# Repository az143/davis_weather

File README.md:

this repository contains all tools necessary for building remote AND online
weather stations using davis vantage vue (or vantage pro) kit.

to be precise, this includes:

* an implementation of the workaround for the infamous "green dot" vendor
lock-in, written in C for a Microchip pic16f88 (without any external
components),

* a data gatherer program (in perl) that fetches the weather readings from a
davis console at configurable intervals, then condenses and uploads the
data to a server on the net,

* a data collector program (in perl) that listens for such uploads and saves the
data in an sqlite database, and optionally uploads it to weather underground
and/or the bom/uk-metoffice weather observations website,

* and a graph generator tool (using gnuplot) and a cgi script to
present readings and graphs. both are written in perl.

there is a little bit of extra documentation on my site at
[http://snafu.priv.at/mystuff/fidobeagle.html](http://snafu.priv.at/mystuff/fidobeagle.html).

all code is (c) 2015 Alexander Zangerl <az@snafu.priv.at>,
and is free and open-source software, licensed under the GPL Version 2.

share and enjoy `:-)`

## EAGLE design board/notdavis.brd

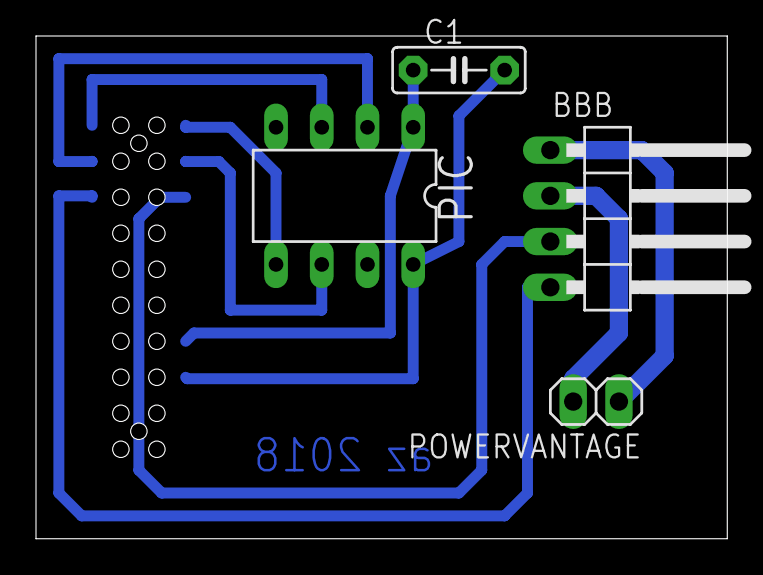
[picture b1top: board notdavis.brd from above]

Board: 2 copper layers, 38.4 x 27.9 mm, 5 parts (1 on the bottom side), 10 nets.

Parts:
BBB: 1X04/90
C1: 0.1uf; C5B2.5
PIC: 16F18313; DIL8
POWERVANTAGE: 1X02
VANTAGE: 79109-20

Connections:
CK: PIC.3, VANTAGE.1
GND: C1.2, PIC.8, VANTAGE.16
MISO: PIC.2, VANTAGE.3
MOSI: PIC.6, VANTAGE.4
unnamed: BBB.2, POWERVANTAGE.2
RXD: BBB.3, VANTAGE.6
SS: PIC.5, VANTAGE.2
TXD: BBB.4, VANTAGE.5
VCC3.3: C1.1, PIC.1, VANTAGE.14
VCC5: BBB.1, POWERVANTAGE.1

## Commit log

2015-11-04 initial publication
2015-11-04 added info re upload to wow and wunderground
2015-11-13 reworked cgi layout a bit, added "daily rain last 14 days" to the tables and to the graphs, updated weatherreceiver to export just the daily rain totals with -R
2016-03-05 added polar windrose graph (needs gnuplot 4.6 or newer)
2016-03-13 updated graph generator for better error output, added windrose graph to weather_cgi
2016-12-01 added dynamic display of links to upload sites (wow and wunderground for now)
2018-09-12 updated xc8 args and clean for newer version (1.45, not ancient 1.12)
2018-10-01 updated for more modern (and cheaper...) pic16f18313
2018-10-28 added board for pic16f18313 implementation
2019-12-16 fetchdavis: applied two patches by Bernhard Reutner-Fischer to handle certain errors and corner cases more robustly
2020-08-26 made new board in kicad (2-layer, too lazy to do more toner transfers...) checkin contains gerber & drill files

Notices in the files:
parts and their libraries:
con-molex-milli-grid: Copyright (C) 2010, Bob Starr
